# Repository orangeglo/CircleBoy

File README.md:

# CircleBoy
CirlceBoy is a small circuit board that lets you replace the directional pad on a gameboy or other device with an analog joystick. CircleBoy was designed specifically to use the 3DS circle pad with a gameboy, but is adaptable to tons of use cases.

## Installation Gallery
A gallery of my installation of the board can be [found here](https://imgur.com/a/vMOLDO8).

## Configuration
You can select between 4 different modes for the stick. Modes are selected by shorting out the dpad contacts in the appropriate direction when you turn the system on. The configuration is stored in the EEPROM of the chip, so you only have to set it once.

Direction | Deadzone | Segments
--- | --- | ---
Up (default) | Small | Balanced
Down          | Large | Balanced
Left          | Small | 3/4 Straight, 1/4 Diagonals
Right         | Large | 3/4 Straight, 1/4 Diagonals

## ATtiny85 Fuses
Since this project uses the reset line on the ATtiny85, once you've written the firmware and enabled the `NO_GOING_BACK_NOW` macro, you'll need to disable the reset on the chip. I did this on my Mac with
```
/Applications/Arduino.app/Contents/Java/hardware/tools/avr/bin/avrdude -C/Applications/Arduino.app/Contents/Java/hardware/tools/avr/etc/avrdude.conf -v -v -v -v -pattiny85 -carduino -P/dev/cu.usbmodem143301 -b19200 -Uhfuse:w:0x5f:m
```
The important part of that is setting the hfuse to 0x5f.

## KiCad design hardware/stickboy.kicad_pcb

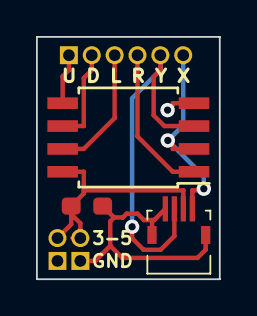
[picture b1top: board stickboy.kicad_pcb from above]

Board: 2 copper layers, 10.2 x 13.5 mm, 6 parts (0 on the bottom side), 8 nets.

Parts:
C1: 0.1 uF; C_0603_1608Metric_Pad1.05x0.95mm_HandSolder
J1, J4: power; PinHeader_1x02_P1.27mm_Vertical
J2: pins; PinHeader_1x06_P1.27mm_Vertical
J3: 59453-041110EDHLF; 59453041110EDHLF
U1: ATtiny85-20SU; SOIJ-8_5.3x5.3mm_P1.27mm

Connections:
GND: C1.2, J1.1, J3.1, J3.MP1, J3.MP2, J4.1, U1.4
unnamed: J2.1, U1.5
unnamed: J2.2, U1.6
unnamed: J2.3, U1.7
unnamed: J2.4, U1.1
unnamed: J2.5, J3.2, U1.3
unnamed: J2.6, J3.4, U1.2
VCC: C1.1, J1.2, J3.3, J4.2, U1.8

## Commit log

2020-03-14 Add firmware
2020-06-18 Add hardware
2020-07-15 fix readme typos, thanks makho you jerk
